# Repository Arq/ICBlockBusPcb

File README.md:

# ICBlockBusPcb

KiCad PCB design of ICBlock Bus with TCA9548 I2C Multiplexer

## Description

## PCB Production costs

* Board size is 40mm x 20mm

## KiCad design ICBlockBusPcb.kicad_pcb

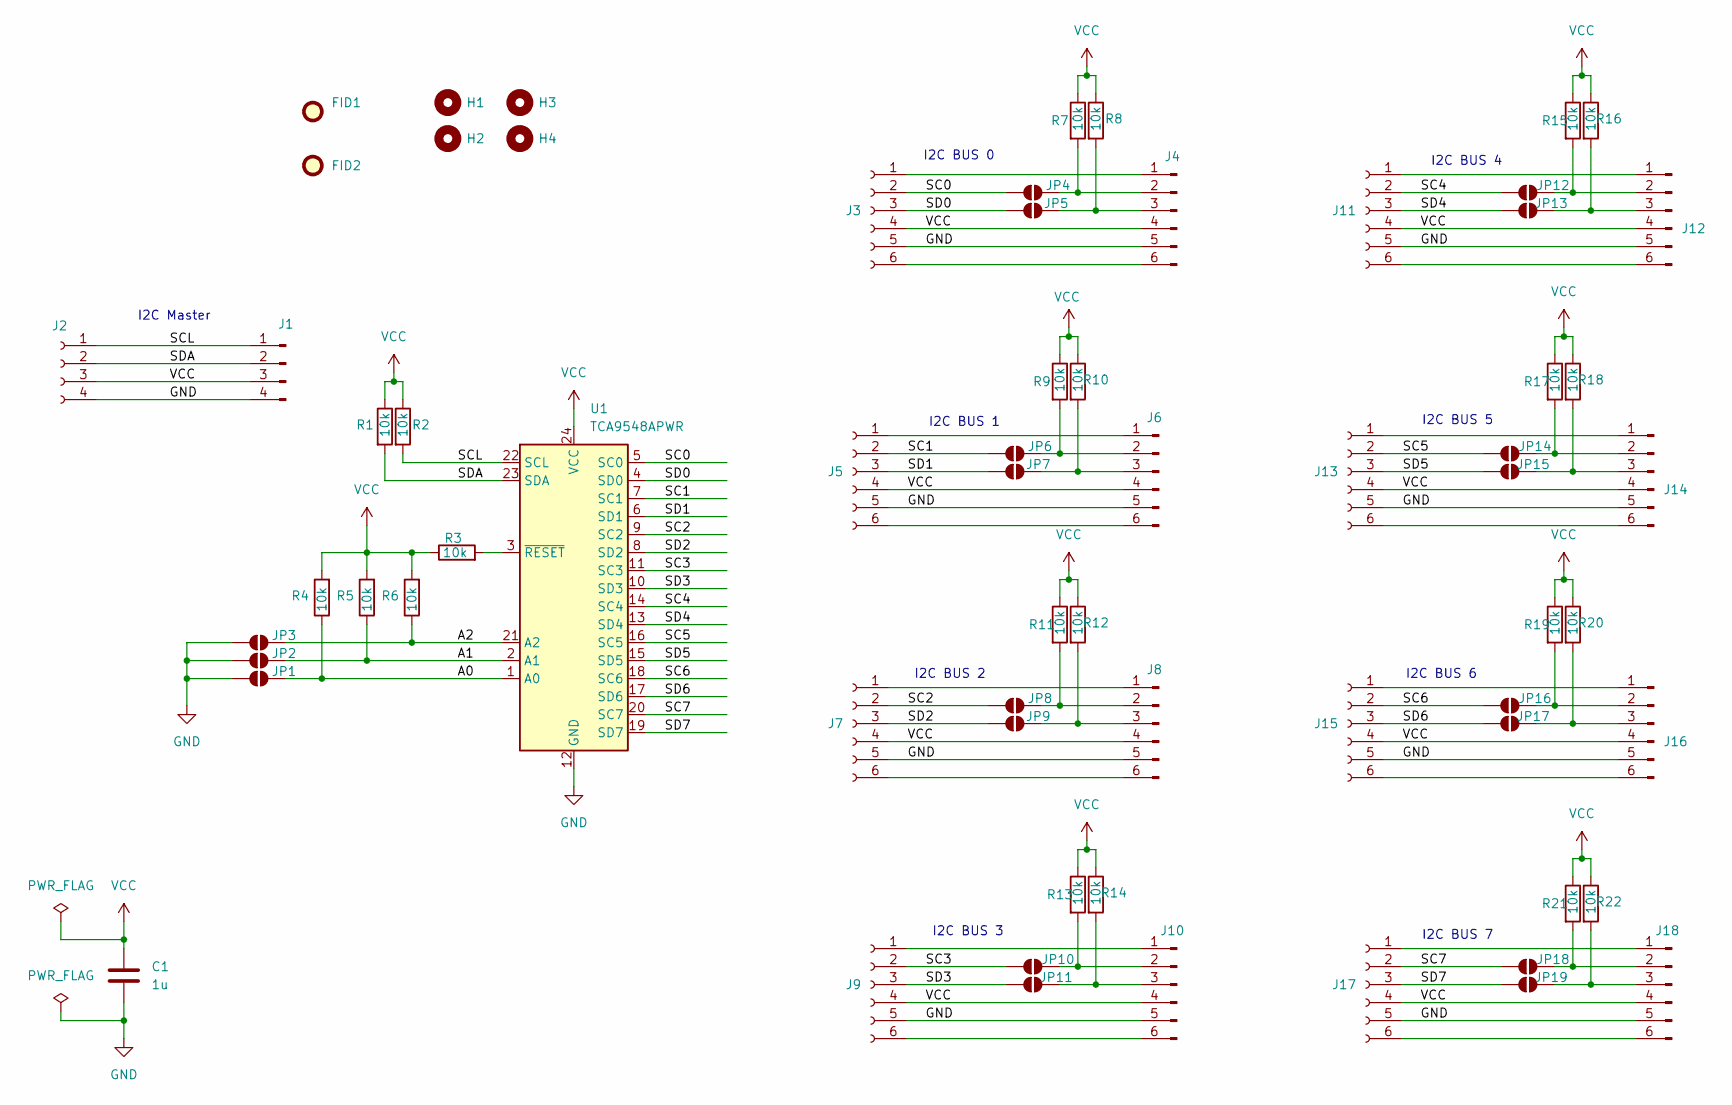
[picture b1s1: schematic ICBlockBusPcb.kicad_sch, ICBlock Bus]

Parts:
C1: 1u; C_1206_3216Metric_Pad1.33x1.80mm_HandSolder
FID1, FID2: Fiducial; Fiducial_0.5mm_Mask1mm
H1, H2, H3, H4: MountingHole; MountingHole_2.2mm_M2
J1: Conn_01x04_Pin; PinHeader_1x04_P2.54mm_Vertical
J2: Conn_01x04_Socket; PinSocket_1x04_P2.54mm_Vertical
J3, J5, J7, J9, J11, J13, J15, J17: Conn_01x06_Socket; PinSocket_1x06_P2.54mm_Vertical
J4, J6, J8, J10, J12, J14, J16, J18: Conn_01x06_Pin; PinHeader_1x06_P2.54mm_Vertical
JP1, JP2, JP3, JP4, JP5, JP6, JP7, JP8, JP9, JP10, JP11, JP12, JP13, JP14, JP15, JP16, JP17, JP18, JP19: SolderJumper_2_Open; SolderJumper-2_P1.3mm_Open_RoundedPad1.0x1.5mm
R1, R2, R3, R4, R5, R6, R7, R8, R9, R10, R11, R12, R13, R14, R15, R16, R17, R18, R19, R20, R21, R22: 10k; R_0805_2012Metric_Pad1.20x1.40mm_HandSolder
U1: TCA9548APWR; TSSOP-24_4.4x7.8mm_P0.65mm

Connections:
/A0: JP1.2 (B), R4.1, U1.1 (A0)
/A1: JP2.2 (B), R5.1, U1.2 (A1)
/A2: JP3.2 (B), R6.1, U1.21 (A2)
/SC0: J3.2, JP4.1 (A), U1.5 (SC0)
/SC1: J5.2, JP6.1 (A), U1.7 (SC1)
/SC2: J7.2, JP8.1 (A), U1.9 (SC2)
/SC3: J9.2, JP10.1 (A), U1.11 (SC3)
/SC4: J11.2, JP12.1 (A), U1.14 (SC4)
/SC5: J13.2, JP14.1 (A), U1.16 (SC5)
/SC6: J15.2, JP16.1 (A), U1.18 (SC6)
/SC7: J17.2, JP18.1 (A), U1.20 (SC7)
/SCL: J1.1, J2.1, R2.2, U1.22 (SCL)
/SD0: J3.3, JP5.1 (A), U1.4 (SD0)
/SD1: J5.3, JP7.1 (A), U1.6 (SD1)
/SD2: J7.3, JP9.1 (A), U1.8 (SD2)
/SD3: J9.3, JP11.1 (A), U1.10 (SD3)
/SD4: J11.3, JP13.1 (A), U1.13 (SD4)
/SD5: J13.3, JP15.1 (A), U1.15 (SD5)
/SD6: J15.3, JP17.1 (A), U1.17 (SD6)
/SD7: J17.3, JP19.1 (A), U1.19 (SD7)
/SDA: J1.2, J2.2, R1.2, U1.23 (SDA)
GND: C1.2, J1.4, J2.4, J3.5, J4.5, J5.5, J6.5, J7.5, J8.5, J9.5, J10.5, J11.5, J12.5, J13.5, J14.5, J15.5, J16.5, J17.5, J18.5, JP1.1 (A), JP2.1 (A), JP3.1 (A), U1.12 (GND)
unnamed: J3.1, J4.1
unnamed: J3.6, J4.6
unnamed: J4.2, JP4.2 (B), R7.2
unnamed: J4.3, JP5.2 (B), R8.2
unnamed: J5.1, J6.1
unnamed: J5.6, J6.6
unnamed: J6.2, JP6.2 (B), R9.2
unnamed: J6.3, JP7.2 (B), R10.2
unnamed: J7.1, J8.1
unnamed: J7.6, J8.6
unnamed: J8.2, JP8.2 (B), R11.2
unnamed: J8.3, JP9.2 (B), R12.2
unnamed: J9.1, J10.1
unnamed: J10.2, JP10.2 (B), R13.2
unnamed: J10.3, JP11.2 (B), R14.2
unnamed: J9.6, J10.6
unnamed: J11.1, J12.1
unnamed: J11.6, J12.6
unnamed: J12.2, JP12.2 (B), R15.2
unnamed: J12.3, JP13.2 (B), R16.2
unnamed: J13.1, J14.1
unnamed: J13.6, J14.6
unnamed: J14.2, JP14.2 (B), R17.2
unnamed: J14.3, JP15.2 (B), R18.2
unnamed: J15.1, J16.1
unnamed: J15.6, J16.6
unnamed: J16.2, JP16.2 (B), R19.2
unnamed: J16.3, JP17.2 (B), R20.2
unnamed: J17.1, J18.1
unnamed: J17.6, J18.6
unnamed: J18.2, JP18.2 (B), R21.2
unnamed: J18.3, JP19.2 (B), R22.2
unnamed: R3.2, U1.3 (~RESET)
VCC: C1.1, J1.3, J2.3, J3.4, J4.4, J5.4, J6.4, J7.4, J8.4, J9.4, J10.4, J11.4, J12.4, J13.4, J14.4, J15.4, J16.4, J17.4, J18.4, R1.1, R2.1, R3.1, R4.2, R5.2, R6.2, R7.1, R8.1, R9.1, R10.1, R11.1, R12.1, R13.1, R14.1, R15.1, R16.1, R17.1, R18.1, R19.1, R20.1, R21.1, R22.1, U1.24 (VCC)

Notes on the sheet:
I2C Master
I2C BUS 7
I2C BUS 1
I2C BUS 5
I2C BUS 6
I2C BUS 0
I2C BUS 4
I2C BUS 2
I2C BUS 3

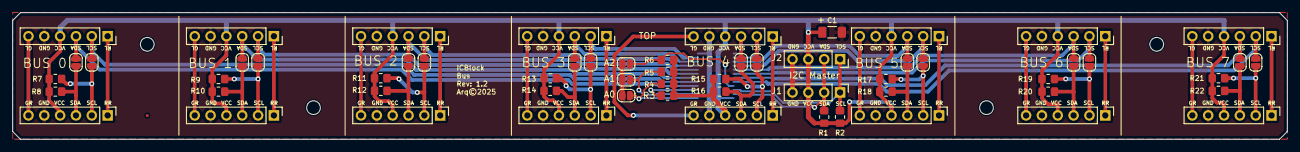
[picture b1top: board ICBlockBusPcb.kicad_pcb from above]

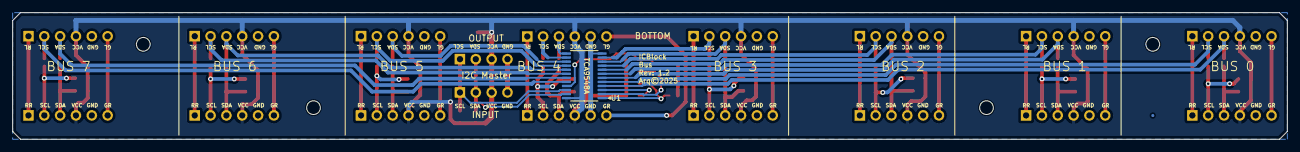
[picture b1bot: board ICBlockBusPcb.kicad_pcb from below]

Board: 2 copper layers, 204.5 x 20.3 mm, 67 parts (2 on the bottom side), 56 nets.

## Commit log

2025-02-15 rev 1.2 gerber
2025-02-16 rev 1.2 prod

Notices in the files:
ICBlockBusPcb.kicad_pcb:
Arq©2025
